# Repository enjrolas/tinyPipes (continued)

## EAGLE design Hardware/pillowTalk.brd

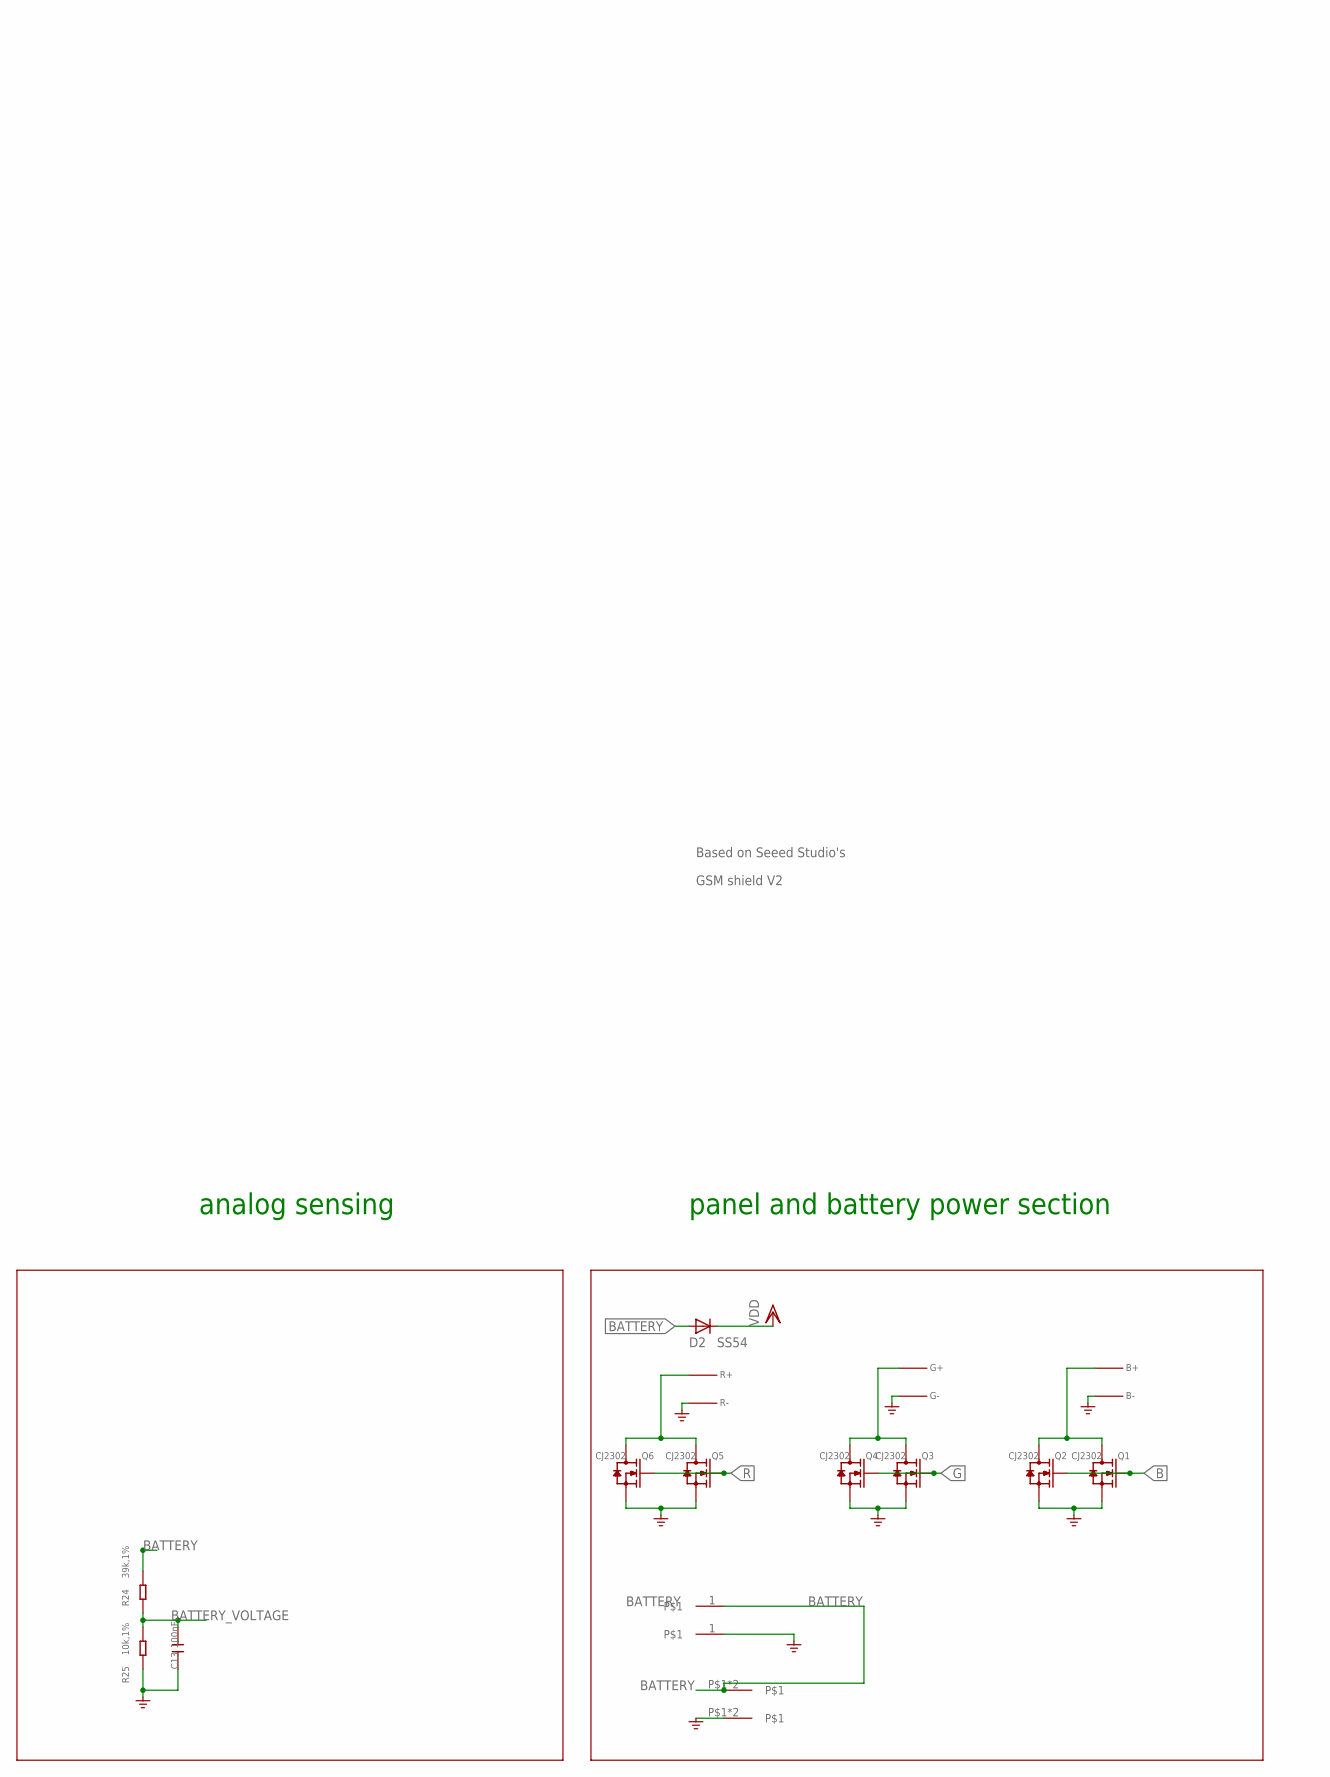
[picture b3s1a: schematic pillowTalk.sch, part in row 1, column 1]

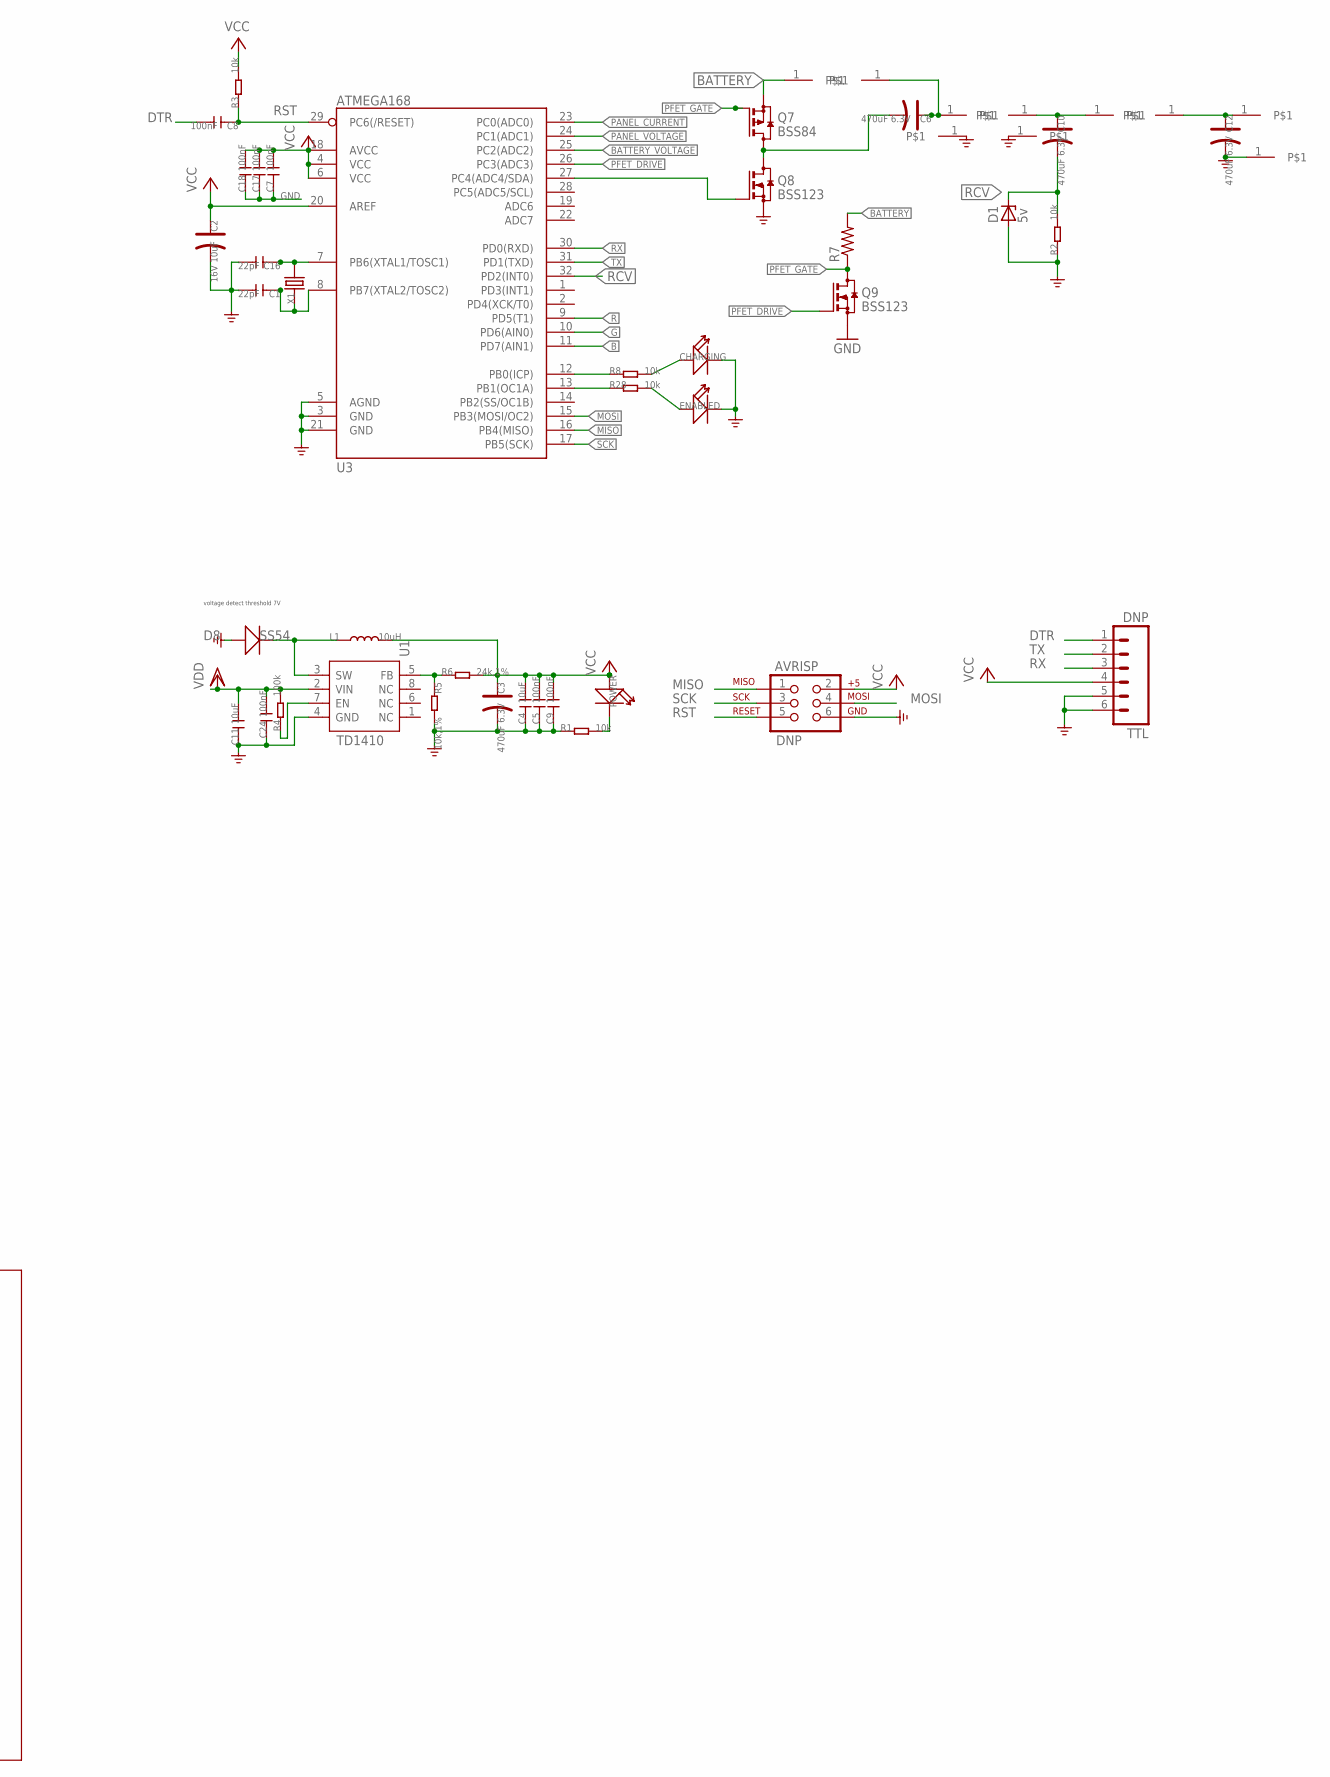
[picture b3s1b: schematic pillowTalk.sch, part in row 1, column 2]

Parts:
AVRISP: DNP; 2X3_LOCK
B+: TINYPIPES_BATTSBATT; TINYPIPES_SBATT
B-: TINYPIPES_BATTSBATT; TINYPIPES_SBATT
BATTERY+: TINYPIPES_BATTBATT; TINYPIPES_BATT
BATTERY-: TINYPIPES_BATTBATT; TINYPIPES_BATT
C1, C16: 22pF; C0603
C2: 16V 10uF; AVX-A
C3, C6, C10, C12: 470uF 6.3V; AVX-D
C4, C11: 10uF; C0805
C5, C7, C8, C9, C13, C17, C18, C24: 100nF; C0603
CHARGING: LED'0603'; LED-0603
D1: 5v; SOD80C
D2, D8: SS54; SMB
ENABLED: LED'0603'; LED-0603
G+: TINYPIPES_BATTSBATT; TINYPIPES_SBATT
G-: TINYPIPES_BATTSBATT; TINYPIPES_SBATT
IN+: TINYPIPES_BATTBATT; TINYPIPES_BATT
IN-: TINYPIPES_BATTBATT; TINYPIPES_BATT
L1: 10uH; L0630
L1+, L1-, L2+, L2-: TINYPIPES_BATTBATT; TINYPIPES_BATT
LOAD+: TINYPIPES_BATTBATT; TINYPIPES_BATT
LOAD-: TINYPIPES_BATTBATT; TINYPIPES_BATT
OUT+: TINYPIPES_BATTBATT; TINYPIPES_BATT
OUT-: TINYPIPES_BATTBATT; TINYPIPES_BATT
PANEL+: TINYPIPES_BATTPANEL; TINYPIPES_PANEL
PANEL-: TINYPIPES_BATTPANEL; TINYPIPES_PANEL
POWER: LED'0603'; LED-0603
Q1, Q2, Q3, Q4, Q5, Q6: CJ2302; SOT23
Q7: BSS84; SOT23
Q8, Q9: BSS123; SOT23
R1, R2, R3, R8, R28: 10k; R0603
R4: 100k; R0603
R5, R25: 10k,1%; R0603
R6: 24k,1%; R0603
R7: R-US_R0603; R0603
R24: 39k,1%; R0603
R+: TINYPIPES_BATTSBATT; TINYPIPES_SBATT
R-: TINYPIPES_BATTSBATT; TINYPIPES_SBATT
TTL: DNP; 1X06_LOCK
U1: TD1410; SOP8
U3: ATMEGA168; TQFP32-08
X1: CRYSTAL'5032'; 2P-SMD-5X3.2

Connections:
B: Q1.1 (G), Q2.1 (G), U3.11 (PD7(AIN1))
BATTERY: BATTERY+.1, D2.A, L1+.1, PANEL+.P$1, PANEL+.P$2, Q7.2 (S), R7.2, R24.2
BATTERY1: C10.+, IN+.1, L2+.1
BATTERY_VOLTAGE: C13.2, R24.1, R25.2, U3.25 (PC2(ADC2))
DTR: C8.2, TTL.1
G: Q3.1 (G), Q4.1 (G), U3.10 (PD6(AIN0))
GND: AVRISP.6, B-.P$1, BATTERY-.1, C1.2, C2.-, C3.-, C4.1, C5.1, C7.1, C9.1, C11.1, C12.-, C13.1, C16.2, C17.1, C18.1, C24.1, CHARGING.-, D1.A, D8.+, ENABLED.-, G-.P$1, IN-.1, LOAD-.1, OUT-.1, PANEL-.P$1, PANEL-.P$2, Q1.2 (S), Q2.2 (S), Q3.2 (S), Q4.2 (S), Q5.2 (S), Q6.2 (S), Q8.2 (S), Q9.2 (S), R1.1, R2.1, R5.2, R25.1, R-.P$1, TTL.5, TTL.6, U1.4 (GND), U3.3 (GND), U3.5 (AGND), U3.21 (GND)
MISO: AVRISP.1, U3.16 (PB4(MISO))
MOSI: AVRISP.4, U3.15 (PB3(MOSI/OC2))
unnamed: C6.-, Q7.3 (D), Q8.3 (D)
unnamed: C16.1, U3.7 (PB6(XTAL1/TOSC1)), X1.2
unnamed: B+.P$1, Q1.3 (D), Q2.3 (D)
unnamed: Q8.1 (G), U3.27 (PC4(ADC4/SDA))
unnamed: G+.P$1, Q3.3 (D), Q4.3 (D)
unnamed: Q5.3 (D), Q6.3 (D), R+.P$1
unnamed: C6.+, L1-.1, OUT+.1
unnamed: POWER.-, R1.2
unnamed: R8.1, U3.12 (PB0(ICP))
unnamed: R4.1, U1.7 (EN)
unnamed: C1.1, U3.8 (PB7(XTAL2/TOSC2)), X1.1
unnamed: R28.1, U3.13 (PB1(OC1A))
unnamed: C12.+, L2-.1, LOAD+.1
unnamed: CHARGING.+, R8.2
unnamed: ENABLED.+, R28.2
unnamed: D8.-, L1.1, U1.3 (SW)
unnamed: R5.1, R6.1, U1.5 (FB)
PANEL_CURRENT: U3.23 (PC0(ADC0))
PANEL_VOLTAGE: U3.24 (PC1(ADC1))
PFET_DRIVE: Q9.1 (G), U3.26 (PC3(ADC3))
PFET_GATE: Q7.1 (G), Q9.3 (D), R7.1
R: Q5.1 (G), Q6.1 (G), U3.9 (PD5(T1))
RCV: C10.-, D1.C, R2.2, U3.32 (PD2(INT0))
RST: AVRISP.5, C8.1, R3.1, U3.29 (PC6(/RESET))
RX: TTL.3, U3.30 (PD0(RXD))
SCK: AVRISP.3, U3.17 (PB5(SCK))
TX: TTL.2, U3.31 (PD1(TXD))
VCC: AVRISP.2, C2.+, C3.+, C4.2, C5.2, C7.2, C9.2, C17.2, C18.2, L1.2, POWER.+, R3.2, R6.2, TTL.4, U3.4 (VCC), U3.6 (VCC), U3.18 (AVCC), U3.20 (AREF)
VDD: C11.2, C24.2, D2.C, R4.2, U1.2 (VIN)

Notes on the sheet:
Based on Seeed Studio's
GSM shield V2
voltage detect threshold 7V
panel and battery power section
analog sensing

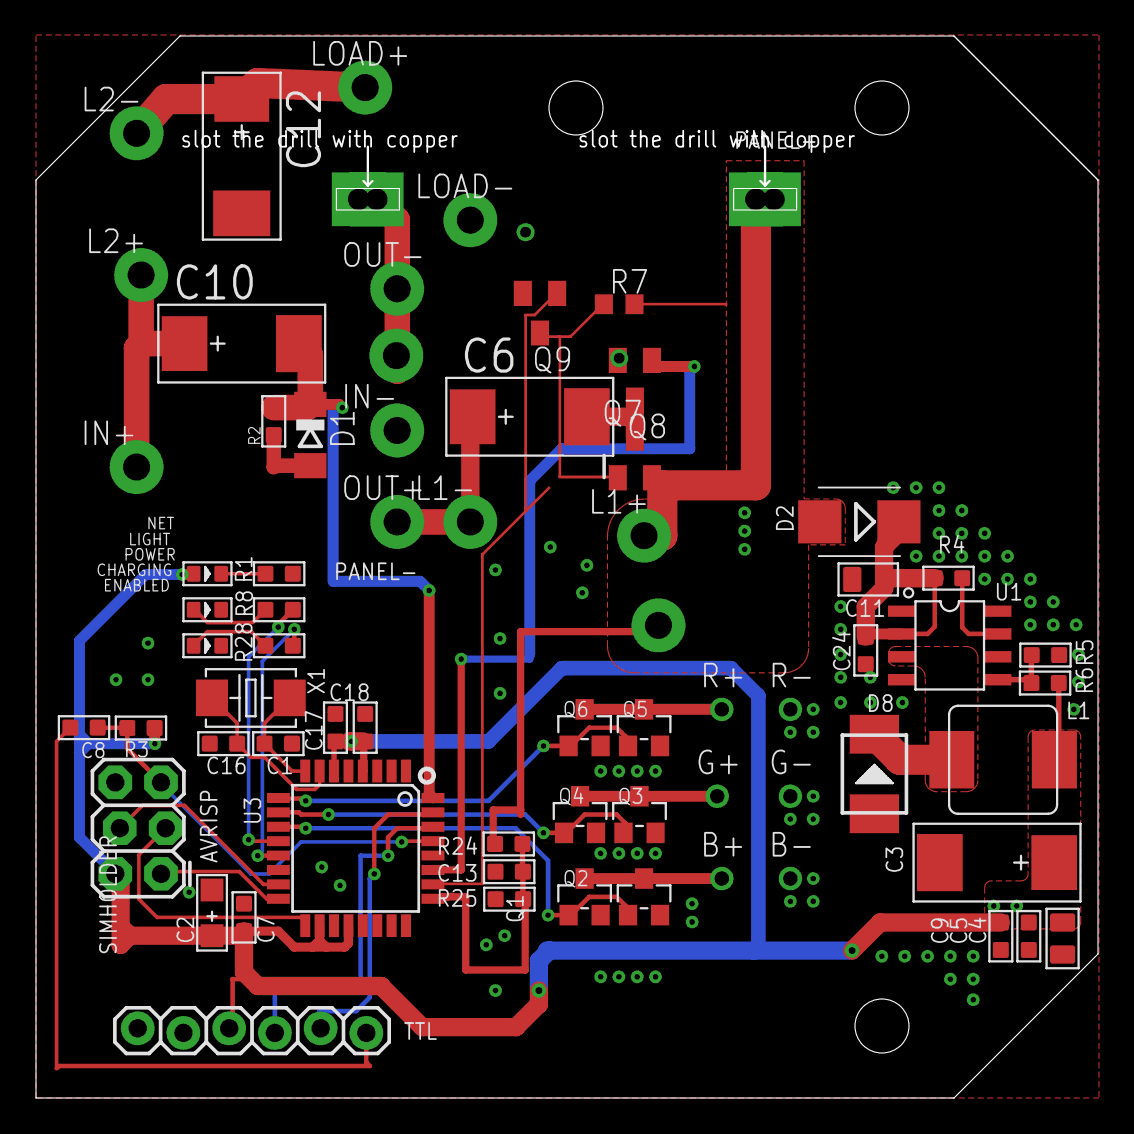
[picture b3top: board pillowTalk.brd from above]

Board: 2 copper layers, 59.0 x 59.0 mm, 69 parts (0 on the bottom side), 36 nets.

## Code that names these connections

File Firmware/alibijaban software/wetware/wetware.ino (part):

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
//#define DEBUG 0

#define PANEL_EN 5
#define PANEL_CURRENT 0
#define PANEL_VOLTAGE 1
#define BATTERY_VOLTAGE 2
#define GSM_POWER 4
#define CHARGING 8 
#define ENABLED 9
#define LOAD_EN 8
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  //run at 9600
  Serial.begin(19200);
  GSM.begin(19200);
  pinMode(PANEL_EN, OUTPUT);
  pinMode(CHARGING, OUTPUT);
  pinMode(ENABLED, OUTPUT);
  pinMode(LOAD_EN, OUTPUT);
  pinMode(GSM_POWER, OUTPUT);
  digitalWrite(CHARGING, HIGH);
  digitalWrite(ENABLED, HIGH);
  digitalWrite(LOAD_EN, HIGH);
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  if(panelPWM<30)  //low panelPWM indicates that we have a high panel voltage and a low current
    {
      if(CV_cycles%300==0)  //check every five minutes to see if we really should be in CV mode
      {  //if we're at low PWM and high voltage (>13V), we're in the right place, and we're topping off the battery
         //low PWM and low voltage is a no-no.  We should be back to CC mode.
      disconnectPanel();
      watchdogDelay(10000);  //wait ten seconds for the battery voltage to settle
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
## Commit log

2014-01-04 first post
2014-01-04 cleaned up a bit
2014-01-04 removing the deleted stuff
2014-01-04 one more renaming
2014-01-06 added RSA library to library folder and decoding sketch to utilities folder
2014-01-06 updated wetware with an added delay in the GSM boot function -- without the delay, it doesn't reboot properly
2014-01-06 added gerber files for the PCB and a signal strength utility in the utilities folder
2014-01-07 removed two LEDs and rearranged remaining three for more board space. Added two more holes for battery leads and a current sense resistor
2014-01-08 moved proto work to proto folder
2014-01-08 added proto folder
2014-01-08 finished routing proto board
2014-01-08 renamed files
2014-01-08 proto rev 1 finished. Added: kelvin sensing, under-voltage limit switch, battery power over-current fuse
2014-01-10 demo initial commit
2014-01-10 finalized routing of demo board, added a quick fix to the PFET drive and board art
2014-01-10 ugh, gotta commit
2014-01-11 merged netRequest and basic HTTP GET code
2014-01-11 moved some files around
2014-01-11 pulled in tinyTinyPipes
2014-01-13 added a tinyBootloader and the streaming library to the libraries section
2014-01-14 added adc_trigger to utilities
2014-01-14 added pwm_panel utility
2014-01-16 netRequest is working really well -- I have the time between requests down to about 5 seconds
2014-01-17 some minor fixes on the demo and proto boards
2014-01-17 added semi-functioning pulse counting PLCC system
2014-01-17 got the pulse timing method to work
2014-01-20 tweaking to try and get the BER down
2014-01-31 pushing up tinyComponents PCB and various firmware changes
2014-02-12 shifted some directories around, adding readmes
2014-02-19 moved tinyTinyPipes to its own branch
2014-02-19 pushing up pillowtalk demo
2014-02-19 cleaned up master
2014-02-19 changed inductor drill size
2014-02-20 stashing latest changes -- still a work in progress
2014-03-06 added test code to wetware and updated the circuit board silkscreen layer to justin bieber riding a unicorn
2014-03-06 oh, yeah -- also have spriso added sprinkler code
2014-03-07 ok, getspray is actually forwarding squirts up the server. It's not a perfect sprinkler yet -- lots of hanging and restarting -- but it's really close
2014-03-07 got a working sprinkler
2014-03-29 got rid of 'instantaneous' response and added more info to 'test' response
2014-03-31 stash
2014-04-03 finished design for tp v3.0, with pillowtalk, power the PCB from the panel, and a PCB antenna
2014-04-11 tinyPipes v3.1
2014-04-11 nagwawala
2014-06-16 push
2014-06-16 Panel Mount Designs
    before June 16
2014-06-18 panel mount
    updated the panel mount design
2014-06-26 added flange
    more stuff
